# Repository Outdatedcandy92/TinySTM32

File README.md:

# TinySTM32

TinySTM32 is a small 30mmx30mm devboard that features a STM32F103T8U6. It has two programmable buttons and LEDs on board, and 18 pins broken out.

## Hardware

[KiCanvas Link](https://kicanvas.org/?repo=https%3A%2F%2Fgithub.com%2FOutdatedcandy92%2FTinySTM32%2Ftree%2Fmain%2Fkicad)
### Schematic

### PCB

### 3D PCB

### Case

The case uses M2 screws to mount the PCB.

## License

This project is licensed under the CERN Open Hardware Licence Version 2 Weakly Reciprocal [(CERN OHL W)](LICENSE.txt)

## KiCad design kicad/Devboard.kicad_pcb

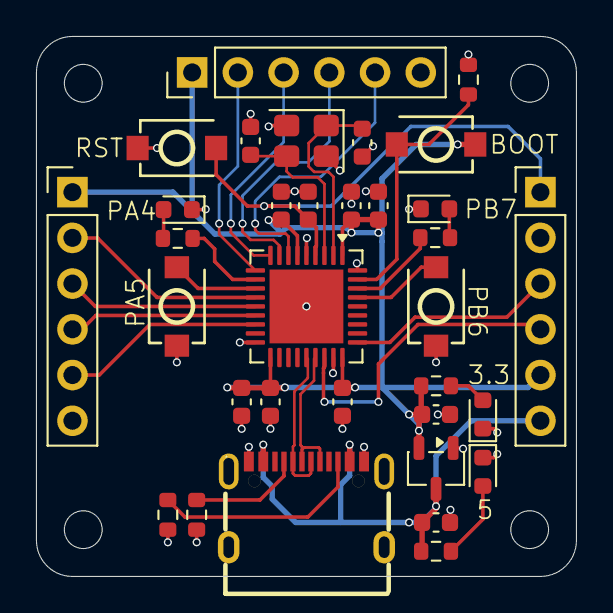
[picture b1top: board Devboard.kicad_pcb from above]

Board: 4 copper layers, 30.0 x 30.0 mm, 37 parts (0 on the bottom side), 29 nets.

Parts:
C1, C2, C7, C8: 1uF; C_0603_1608Metric
C3, C4, C5, C6, C11: 100nF; C_0603_1608Metric
C9, C10: 15pF; C_0603_1608Metric
D1, D2, D3, D4: LED; LED_0603_1608Metric
H1, H2, H3, H4: MountingHole; MountingHole_2.1mm
J1: USB_C_Receptacle_USB2.0_16P; USB-C-SMD_TYPE-C-16PIN-2MD-073
J2, J3, J4: Conn_01x06; PinHeader_1x06_P2.54mm_Vertical
R1, R2: 5.1K; R_0603_1608Metric
R3, R4, R5, R6, R7: 10K; R_0603_1608Metric
SW1: RESET; SW-SMD_L3.9-W3.0-P4.45
SW2: BOOT; SW-SMD_L3.9-W3.0-P4.45
SW3: BTN1; SW-SMD_L3.9-W3.0-P4.45
SW4: BTN2; SW-SMD_L3.9-W3.0-P4.45
U1: XC6206PxxxMR; SOT-23-3
U2: STM32F103T8Ux; QFN-36-1EP_6x6mm_P0.5mm_EP4.1x4.1mm
Y1: 8Mhz; Crystal_SMD_3225-4Pin_3.2x2.5mm

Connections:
+3V3: C2.1, C3.1, C4.1, C5.1, C6.1, C7.1, C8.1, J2.1, J3.1, J4.5, R5.2, SW2.1, U1.2 (VO), U2.1 (VDD), U2.6 (VDDA), U2.19 (VDD), U2.27 (VDD)
/BOOT: R3.1, SW2.2, U2.35 (BOOT0)
/BTN1: SW3.2, U2.33 (PB6)
/BTN2: SW4.2, U2.12 (PA5)
/NRST: C11.1, J4.1, SW1.2, U2.4 (NRST)
/PA0: J3.5, U2.7 (PA0)
/PA1: J3.4, U2.8 (PA1)
/PA2: J3.3, U2.9 (PA2)
/PA3: J3.2, U2.10 (PA3)
/PA4: R7.2, U2.11 (PA4)
/PA6: J2.2, U2.13 (PA6)
/PA7: J2.3, U2.14 (PA7)
/PB0: J2.4, U2.15 (PB0)
/PB1: J2.5, U2.16 (PB1)
/PB7: R4.2, U2.34 (PB7)
/SWCLK: J4.3, U2.28 (PA14)
/SWDIO: J4.4, U2.25 (PA13)
/USB_D+: J1.A6 (D+), J1.B6 (D+), U2.24 (PA12)
/USB_D-: J1.A7 (D-), J1.B7 (D-), U2.23 (PA11)
/XIN: C10.1, U2.2 (PD0), Y1.1
/XOUT: C9.1, U2.3 (PD1), Y1.3
GND: C1.2, C2.2, C3.2, C4.2, C5.2, C6.2, C7.2, C8.2, C9.2, C10.2, C11.2, D1.1 (K), D2.1 (K), D3.1 (K), D4.1 (K), J1.A1 (GND), J1.B1 (GND), J2.6, J3.6, J4.2, R1.2, R2.2, R3.2, SW1.1, SW3.1, SW4.1, U1.1 (GND), U2.5 (VSSA), U2.18 (VSS), U2.26 (VSS), U2.36 (VSS), U2.37 (VSS), Y1.2 (G), Y1.4 (G)
unnamed: D1.2 (A), R6.1
unnamed: D2.2 (A), R5.1
unnamed: D3.2 (A), R4.1
unnamed: D4.2 (A), R7.1
unnamed: J1.A5 (CC1), R2.1
unnamed: J1.B5 (CC2), R1.1
VBUS: C1.1, J1.A4 (VBUS), J1.B4 (VBUS), J4.6, R6.2, U1.3 (VI)

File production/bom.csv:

Designator,Footprint,Quantity,Value,LCSC Part #
"C1, C2, C7, C8",0603,4,1uF,
"C10, C9",0603,2,15pF,
"C11, C3, C4, C5, C6",0603,5,100nF,
"D1, D2, D3, D4",0603,4,LED,
J1,USB-C-SMD_TYPE-C-16PIN-2MD-073,1,USB_C_Receptacle_USB2.0_16P,C2765186
"J2, J3, J4",PinHeader_1x06_P2.54mm_Vertical,3,Conn_01x06,
"R1, R2",0603,2,5.1K,
"R3, R4, R5, R6, R7",0603,5,10K,
SW1,SW-SMD_L3.9-W3.0-P4.45,1,RESET,
SW2,SW-SMD_L3.9-W3.0-P4.45,1,BOOT,
SW3,SW-SMD_L3.9-W3.0-P4.45,1,BTN1,
SW4,SW-SMD_L3.9-W3.0-P4.45,1,BTN2,
U1,SOT-23-3,1,XC6206PxxxMR,
U2,QFN-36-1EP_6x6mm_P0.5mm_EP4.1x4.1mm,1,STM32F103T8Ux,
Y1,Crystal_SMD_3225-4Pin_3.2x2.5mm,1,8Mhz,

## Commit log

2026-05-05 KiCanvas Link
2026-05-05 fix license link in readme
2026-05-11 case
